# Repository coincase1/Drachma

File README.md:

30% Left-Handed Hall Effect Keypad

Based on / Inspired by [Peppapigh's HE60](https://github.com/peppapighs/HE60).

This keyboard is a PCB swap of the [Kisnt 34 Key Numpad](https://www.amazon.com/gp/product/B0C1H8V52D?smid=A1QSA46GV4FLI2&psc=1). With modifications to the top of the case using a hobby saw, this PCB fits inside of that case. The Drachma PCB connects to the Kisnt USB daughterboard using the provided Flat Conductor Cable. It also features a connection for a Pico-EZmate connector featured on Unified Daughterboards.

For anyone looking at this design at a later date, please be mindful of the Analog-to-Digital pins on the STM32F446 microcontroller. These can be verified on Sheets 46-56 of the STM32F446T MC Manual.

For HE switches, my recommendation are either OH49E-S or SS39ET from Honeywell. The OH49E-S are clones of these switches and these are featured in a number of big box HE board builds.

All Kicad and Firmware represents the latest (V3) Drachma build.

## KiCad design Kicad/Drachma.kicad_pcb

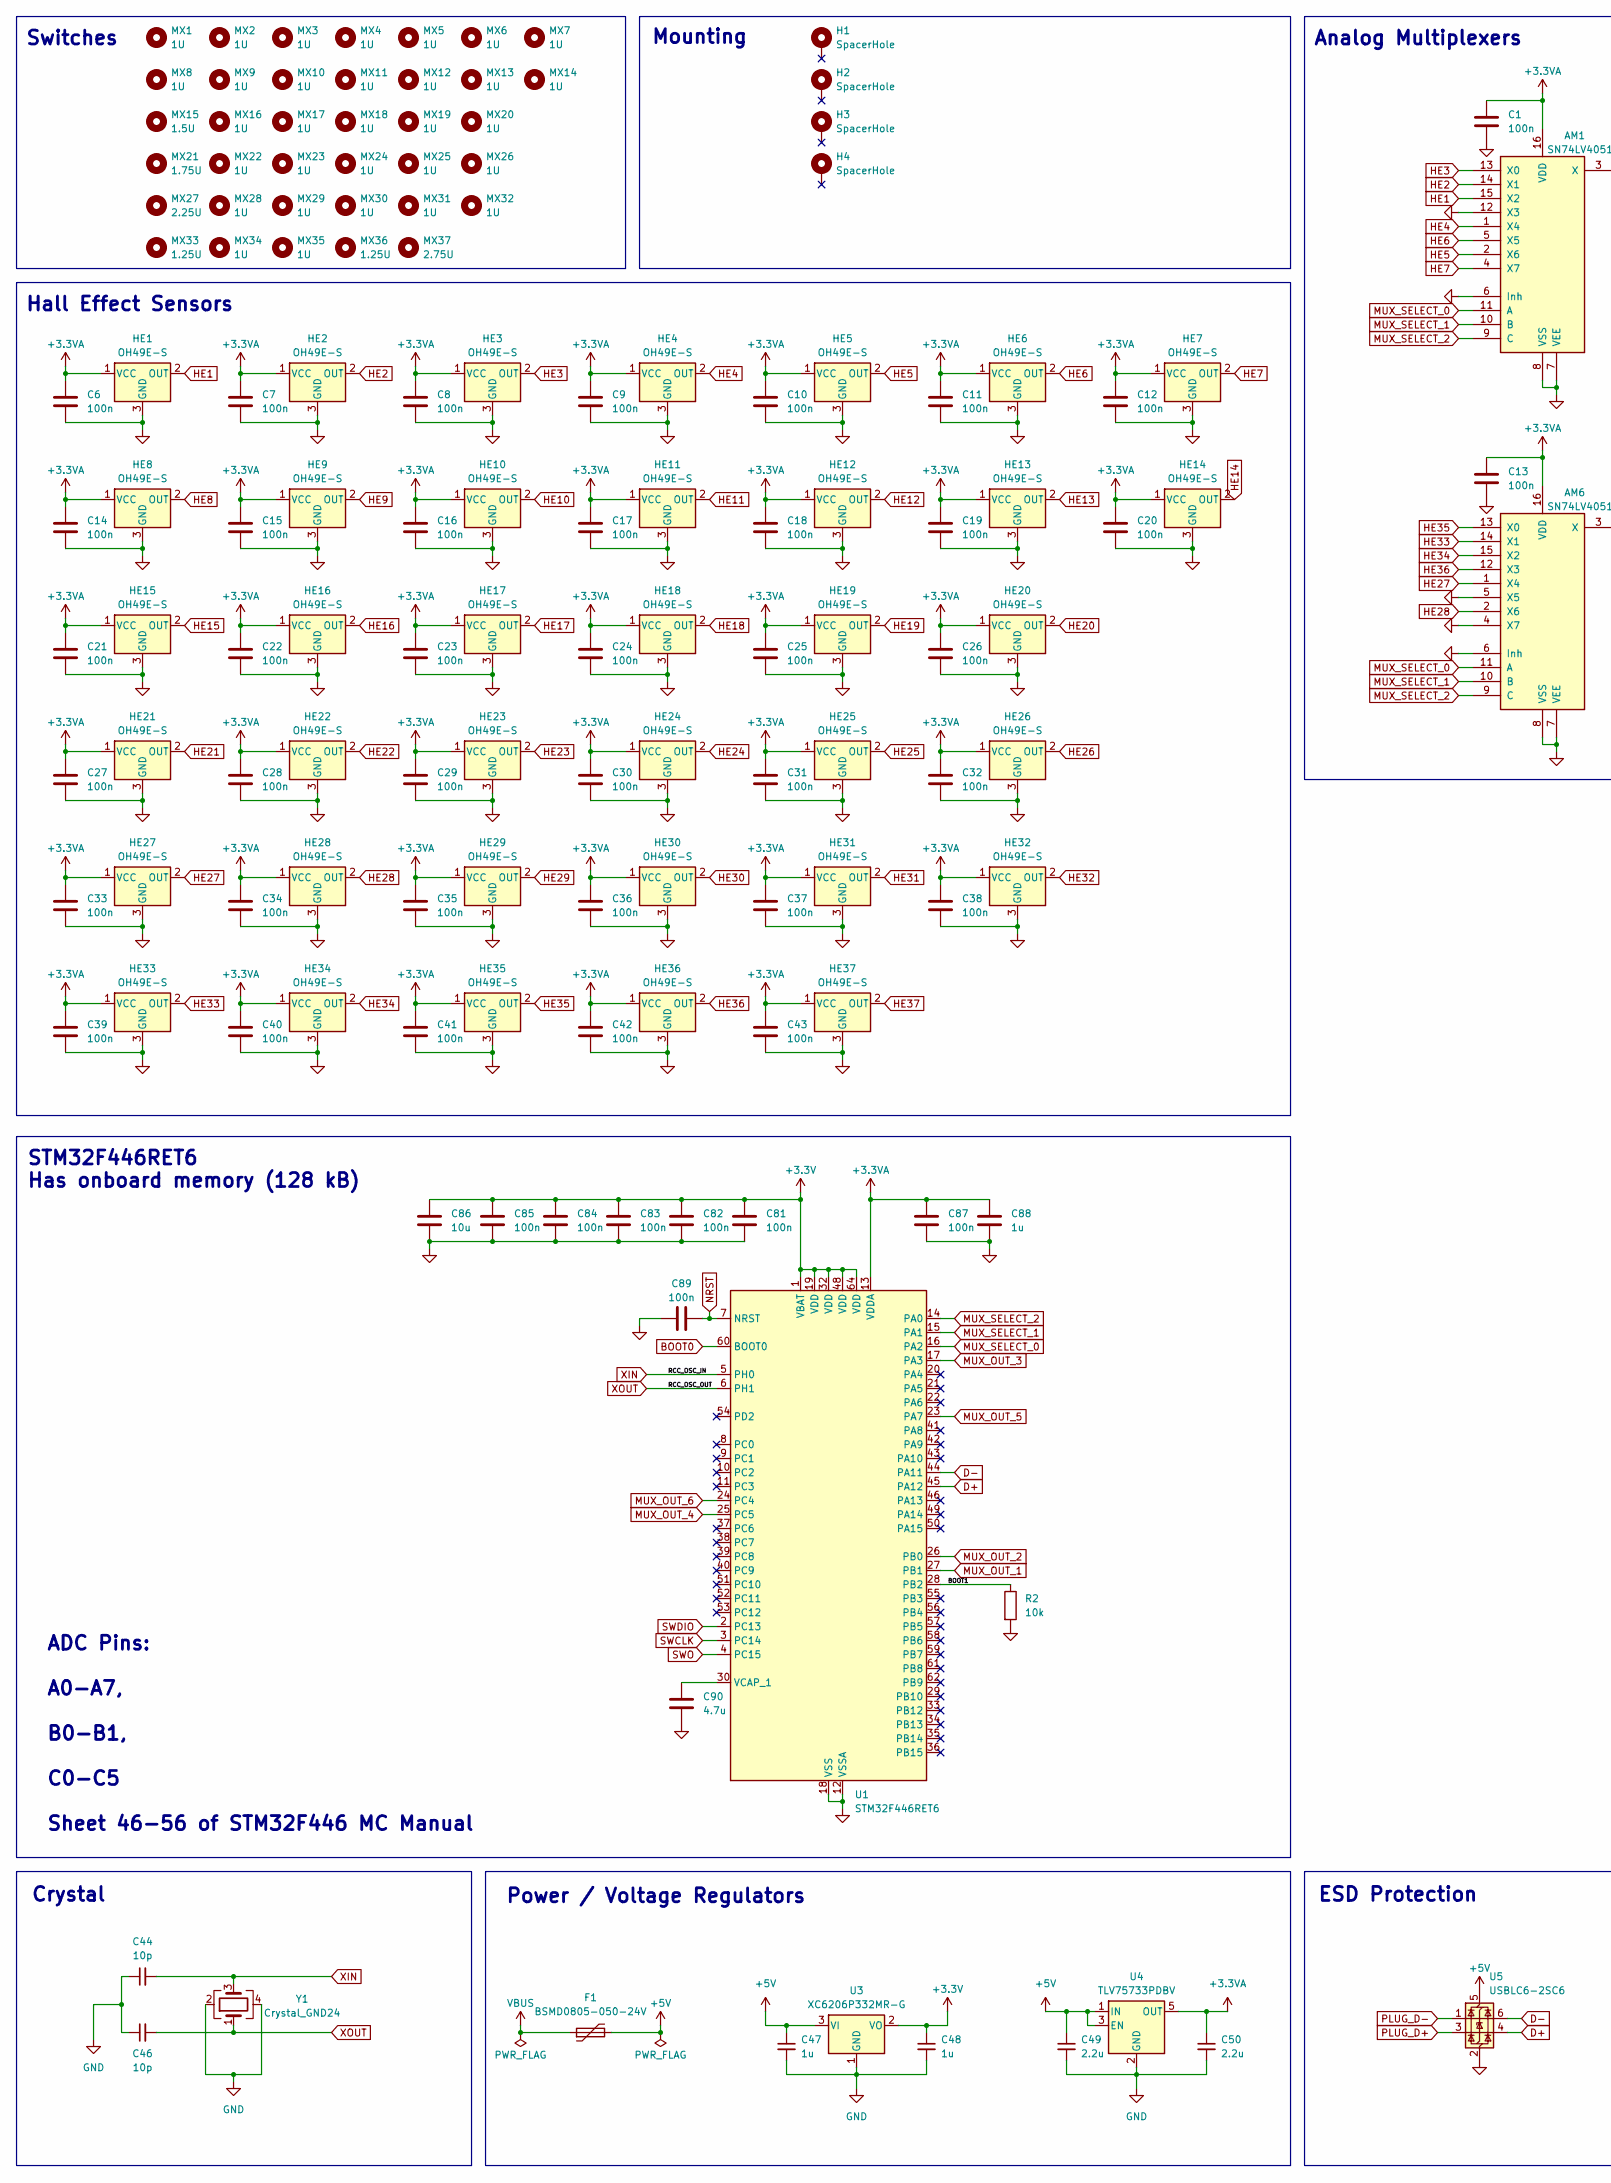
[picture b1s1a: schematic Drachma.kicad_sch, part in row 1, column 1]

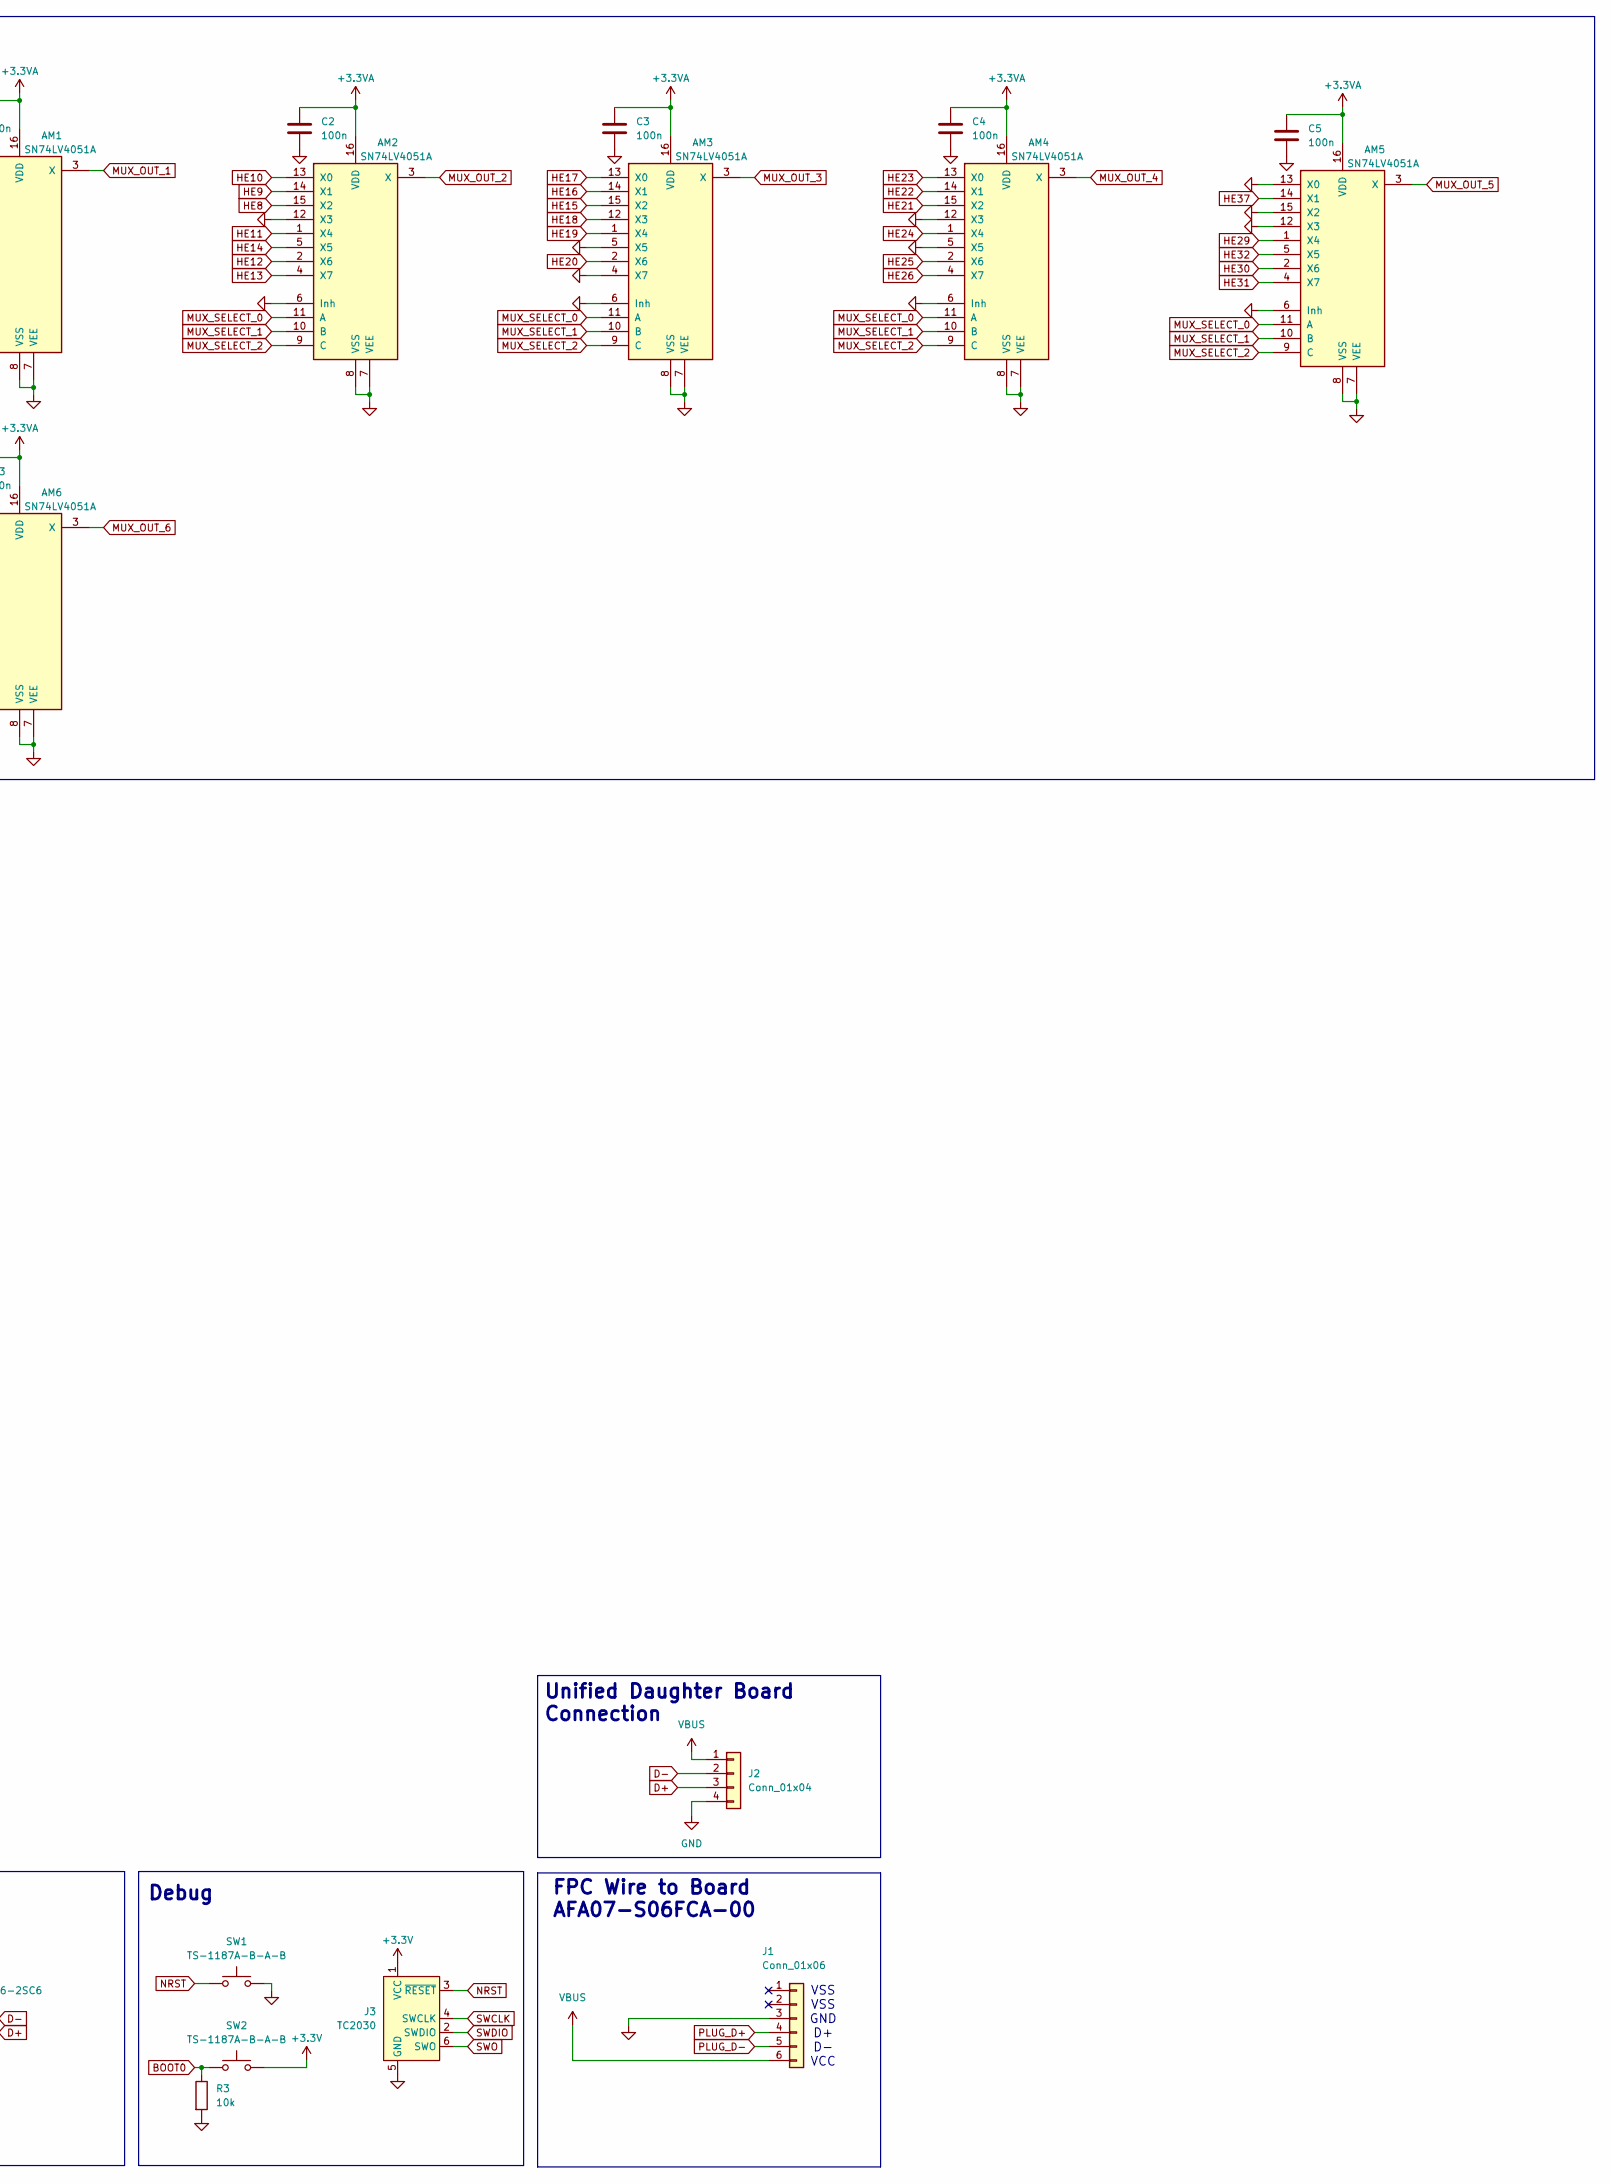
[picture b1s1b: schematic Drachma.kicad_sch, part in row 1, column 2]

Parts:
AM1, AM2, AM3, AM4, AM5, AM6: SN74LV4051A; TSSOP-16_4.4x5mm_P0.65mm
C1, C2, C3, C4, C5, C6, C7, C8, C9, C10, C11, C12, C13, C14, C15, C16, C17, C18, C19, C20, C21, C22, C23, C24, C25, C26, C27, C28, C29, C30, C31, C32, C33, C34, C35, C36, C37, C38, C39, C40, C41, C42, C43, C81, C82, C83, C84, C85, C87, C89: 100n; C_0402_1005Metric
C44, C46: 10p; C_0402_1005Metric
C47, C48, C88: 1u; C_0603_1608Metric
C49, C50: 2.2u; C_0603_1608Metric
C86: 10u; C_0603_1608Metric
C90: 4.7u; C_0603_1608Metric
F1: BSMD0805-050-24V; Fuse_0805_2012Metric
H1, H2, H3, H4: SpacerHole; MountingHole_2.2mm_M2_Pad
HE1, HE2, HE3, HE4, HE5, HE6, HE7, HE8, HE9, HE10, HE11, HE12, HE13, HE14, HE15, HE16, HE17, HE18, HE19, HE20, HE21, HE22, HE23, HE24, HE25, HE26, HE27, HE28, HE29, HE30, HE31, HE32, HE33, HE34, HE35, HE36, HE37: OH49E-S; SOT-23-3
J1: Conn_01x06; JUSHUO_AFA07-S06FCA-00_1x6-1MP_P1.0mm_Horizontal
J2: Conn_01x04; Molex_Pico-EZmate_78171-0004_1x04-1MP_P1.20mm_Vertical
J3: TC2030; Tag-Connect_TC2030-IDC-FP_2x03_P1.27mm_Vertical
MX1, MX2, MX3, MX4, MX5, MX6, MX7, MX8, MX9, MX10, MX11, MX12, MX13, MX14, MX16, MX17, MX18, MX19, MX20, MX22, MX23, MX24, MX25, MX26, MX28, MX29, MX30, MX31, MX32, MX34, MX35: 1U; MX-1U
MX15: 1.5U; MX-1.5U
MX21: 1.75U; MX-1.75U
MX27: 2.25U; MX-2.25U
MX33, MX36: 1.25U; MX-1.25U
MX37: 2.75U; MX-2.75U-ReversedStabilizers
R2, R3: 10k; R_0402_1005Metric
SW1, SW2: TS-1187A-B-A-B; SW_Push_1P1T_XKB_TS-1187A
U1: STM32F446RET6; LQFP-64_10x10mm_P0.5mm
U3: XC6206P332MR-G; SOT-23-3
U4: TLV75733PDBV; SOT-23-5
U5: USBLC6-2SC6; SOT-23-6
Y1: Crystal_GND24; Crystal_SMD_3225-4Pin_3.2x2.5mm

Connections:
+3.3V: C48.1, C81.1, C82.1, C83.1, C84.1, C85.1, C86.1, J3.1 (VCC), SW2.2, U1.1 (VBAT), U1.19 (VDD), U1.32 (VDD), U1.48 (VDD), U1.64 (VDD), U3.2 (VO)
+3.3VA: AM1.16 (VDD), AM2.16 (VDD), AM3.16 (VDD), AM4.16 (VDD), AM5.16 (VDD), AM6.16 (VDD), C1.1, C2.1, C3.1, C4.1, C5.1, C6.1, C7.1, C8.1, C9.1, C10.1, C11.1, C12.1, C13.1, C14.1, C15.1, C16.1, C17.1, C18.1, C19.1, C20.1, C21.1, C22.1, C23.1, C24.1, C25.1, C26.1, C27.1, C28.1, C29.1, C30.1, C31.1, C32.1, C33.1, C34.1, C35.1, C36.1, C37.1, C38.1, C39.1, C40.1, C41.1, C42.1, C43.1, C50.1, C87.1, C88.1, HE1.1 (VCC), HE2.1 (VCC), HE3.1 (VCC), HE4.1 (VCC), HE5.1 (VCC), HE6.1 (VCC), HE7.1 (VCC), HE8.1 (VCC), HE9.1 (VCC), HE10.1 (VCC), HE11.1 (VCC), HE12.1 (VCC), HE13.1 (VCC), HE14.1 (VCC), HE15.1 (VCC), HE16.1 (VCC), HE17.1 (VCC), HE18.1 (VCC), HE19.1 (VCC), HE20.1 (VCC), HE21.1 (VCC), HE22.1 (VCC), HE23.1 (VCC), HE24.1 (VCC), HE25.1 (VCC), HE26.1 (VCC), HE27.1 (VCC), HE28.1 (VCC), HE29.1 (VCC), HE30.1 (VCC), HE31.1 (VCC), HE32.1 (VCC), HE33.1 (VCC), HE34.1 (VCC), HE35.1 (VCC), HE36.1 (VCC), HE37.1 (VCC), U1.13 (VDDA), U4.5 (OUT)
+5V: C47.1, C49.1, F1.2, U3.3 (VI), U4.1 (IN), U4.3 (EN), U5.5 (VBUS)
/BOOT1: R2.1, U1.28 (PB2)
BOOT0: R3.1, SW2.1, U1.60 (BOOT0)
D+: J2.3, U1.45 (PA12), U5.4 (I/O2)
D-: J2.2, U1.44 (PA11), U5.6 (I/O1)
GND: AM1.6 (Inh), AM1.7 (VEE), AM1.8 (VSS), AM1.12 (X3), AM2.6 (Inh), AM2.7 (VEE), AM2.8 (VSS), AM2.12 (X3), AM3.4 (X7), AM3.5 (X5), AM3.6 (Inh), AM3.7 (VEE), AM3.8 (VSS), AM4.5 (X5), AM4.6 (Inh), AM4.7 (VEE), AM4.8 (VSS), AM4.12 (X3), AM5.6 (Inh), AM5.7 (VEE), AM5.8 (VSS), AM5.12 (X3), AM5.13 (X0), AM5.15 (X2), AM6.4 (X7), AM6.5 (X5), AM6.6 (Inh), AM6.7 (VEE), AM6.8 (VSS), C1.2, C2.2, C3.2, C4.2, C5.2, C6.2, C7.2, C8.2, C9.2, C10.2, C11.2, C12.2, C13.2, C14.2, C15.2, C16.2, C17.2, C18.2, C19.2, C20.2, C21.2, C22.2, C23.2, C24.2, C25.2, C26.2, C27.2, C28.2, C29.2, C30.2, C31.2, C32.2, C33.2, C34.2, C35.2, C36.2, C37.2, C38.2, C39.2, C40.2, C41.2, C42.2, C43.2, C44.1, C46.1, C47.2, C48.2, C49.2, C50.2, C81.2, C82.2, C83.2, C84.2, C85.2, C86.2, C87.2, C88.2, C89.1, C90.2, HE1.3 (GND), HE2.3 (GND), HE3.3 (GND), HE4.3 (GND), HE5.3 (GND), HE6.3 (GND), HE7.3 (GND), HE8.3 (GND), HE9.3 (GND), HE10.3 (GND), HE11.3 (GND), HE12.3 (GND), HE13.3 (GND), HE14.3 (GND), HE15.3 (GND), HE16.3 (GND), HE17.3 (GND), HE18.3 (GND), HE19.3 (GND), HE20.3 (GND), HE21.3 (GND), HE22.3 (GND), HE23.3 (GND), HE24.3 (GND), HE25.3 (GND), HE26.3 (GND), HE27.3 (GND), HE28.3 (GND), HE29.3 (GND), HE30.3 (GND), HE31.3 (GND), HE32.3 (GND), HE33.3 (GND), HE34.3 (GND), HE35.3 (GND), HE36.3 (GND), HE37.3 (GND), J1.3, J2.4, J3.5 (GND), R2.2, R3.2, SW1.2, U1.12 (VSSA), U1.18 (VSS), U1.31 (VSS), U1.47 (VSS), U1.63 (VSS), U3.1 (GND), U4.2 (GND), U5.2 (GND), Y1.2, Y1.4
HE1: AM1.15 (X2), HE1.2 (OUT)
HE2: AM1.14 (X1), HE2.2 (OUT)
HE3: AM1.13 (X0), HE3.2 (OUT)
HE4: AM1.1 (X4), HE4.2 (OUT)
HE5: AM1.2 (X6), HE5.2 (OUT)
HE6: AM1.5 (X5), HE6.2 (OUT)
HE7: AM1.4 (X7), HE7.2 (OUT)
HE8: AM2.15 (X2), HE8.2 (OUT)
HE9: AM2.14 (X1), HE9.2 (OUT)
HE10: AM2.13 (X0), HE10.2 (OUT)
HE11: AM2.1 (X4), HE11.2 (OUT)
HE12: AM2.2 (X6), HE12.2 (OUT)
HE13: AM2.4 (X7), HE13.2 (OUT)
HE14: AM2.5 (X5), HE14.2 (OUT)
HE15: AM3.15 (X2), HE15.2 (OUT)
HE16: AM3.14 (X1), HE16.2 (OUT)
HE17: AM3.13 (X0), HE17.2 (OUT)
HE18: AM3.12 (X3), HE18.2 (OUT)
HE19: AM3.1 (X4), HE19.2 (OUT)
HE20: AM3.2 (X6), HE20.2 (OUT)
HE21: AM4.15 (X2), HE21.2 (OUT)
HE22: AM4.14 (X1), HE22.2 (OUT)
HE23: AM4.13 (X0), HE23.2 (OUT)
HE24: AM4.1 (X4), HE24.2 (OUT)
HE25: AM4.2 (X6), HE25.2 (OUT)
HE26: AM4.4 (X7), HE26.2 (OUT)
HE27: AM6.1 (X4), HE27.2 (OUT)
HE28: AM6.2 (X6), HE28.2 (OUT)
HE29: AM5.1 (X4), HE29.2 (OUT)
HE30: AM5.2 (X6), HE30.2 (OUT)
HE31: AM5.4 (X7), HE31.2 (OUT)
HE32: AM5.5 (X5), HE32.2 (OUT)
HE33: AM6.14 (X1), HE33.2 (OUT)
HE34: AM6.15 (X2), HE34.2 (OUT)
HE35: AM6.13 (X0), HE35.2 (OUT)
HE36: AM6.12 (X3), HE36.2 (OUT)
HE37: AM5.14 (X1), HE37.2 (OUT)
MUX_OUT_1: AM1.3 (X), U1.27 (PB1)
MUX_OUT_2: AM2.3 (X), U1.26 (PB0)
MUX_OUT_3: AM3.3 (X), U1.17 (PA3)
MUX_OUT_4: AM4.3 (X), U1.25 (PC5)
MUX_OUT_5: AM5.3 (X), U1.23 (PA7)
MUX_OUT_6: AM6.3 (X), U1.24 (PC4)
MUX_SELECT_0: AM1.11 (A), AM2.11 (A), AM3.11 (A), AM4.11 (A), AM5.11 (A), AM6.11 (A), U1.16 (PA2)
MUX_SELECT_1: AM1.10 (B), AM2.10 (B), AM3.10 (B), AM4.10 (B), AM5.10 (B), AM6.10 (B), U1.15 (PA1)
MUX_SELECT_2: AM1.9 (C), AM2.9 (C), AM3.9 (C), AM4.9 (C), AM5.9 (C), AM6.9 (C), U1.14 (PA0)
NRST: C89.2, J3.3 (~RESET), SW1.1, U1.7 (NRST)
unnamed: C90.1, U1.30 (VCAP_1)
PLUG_D+: J1.4, U5.3 (I/O2)
PLUG_D-: J1.5, U5.1 (I/O1)
SWCLK: J3.4 (SWCLK), U1.3 (PC14)
SWDIO: J3.2 (SWDIO), U1.2 (PC13)
SWO: J3.6 (SWO), U1.4 (PC15)
VBUS: F1.1, J1.6, J2.1
XIN: C44.2, U1.5 (PH0), Y1.3
XOUT: C46.2, U1.6 (PH1), Y1.1

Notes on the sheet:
VSS VSS GND D+ D- VCC
STM32F446RET6 Has onboard memory (128 kB)
Mounting
ESD Protection
Switches
FPC Wire to Board AFA07-S06FCA-00
ADC Pins: A0-A7, B0-B1, C0-C5 Sheet 46-56 of STM32F446 MC Manual
Analog Multiplexers
Hall Effect Sensors
Unified Daughter Board Connection
Power / Voltage Regulators
Crystal
Debug

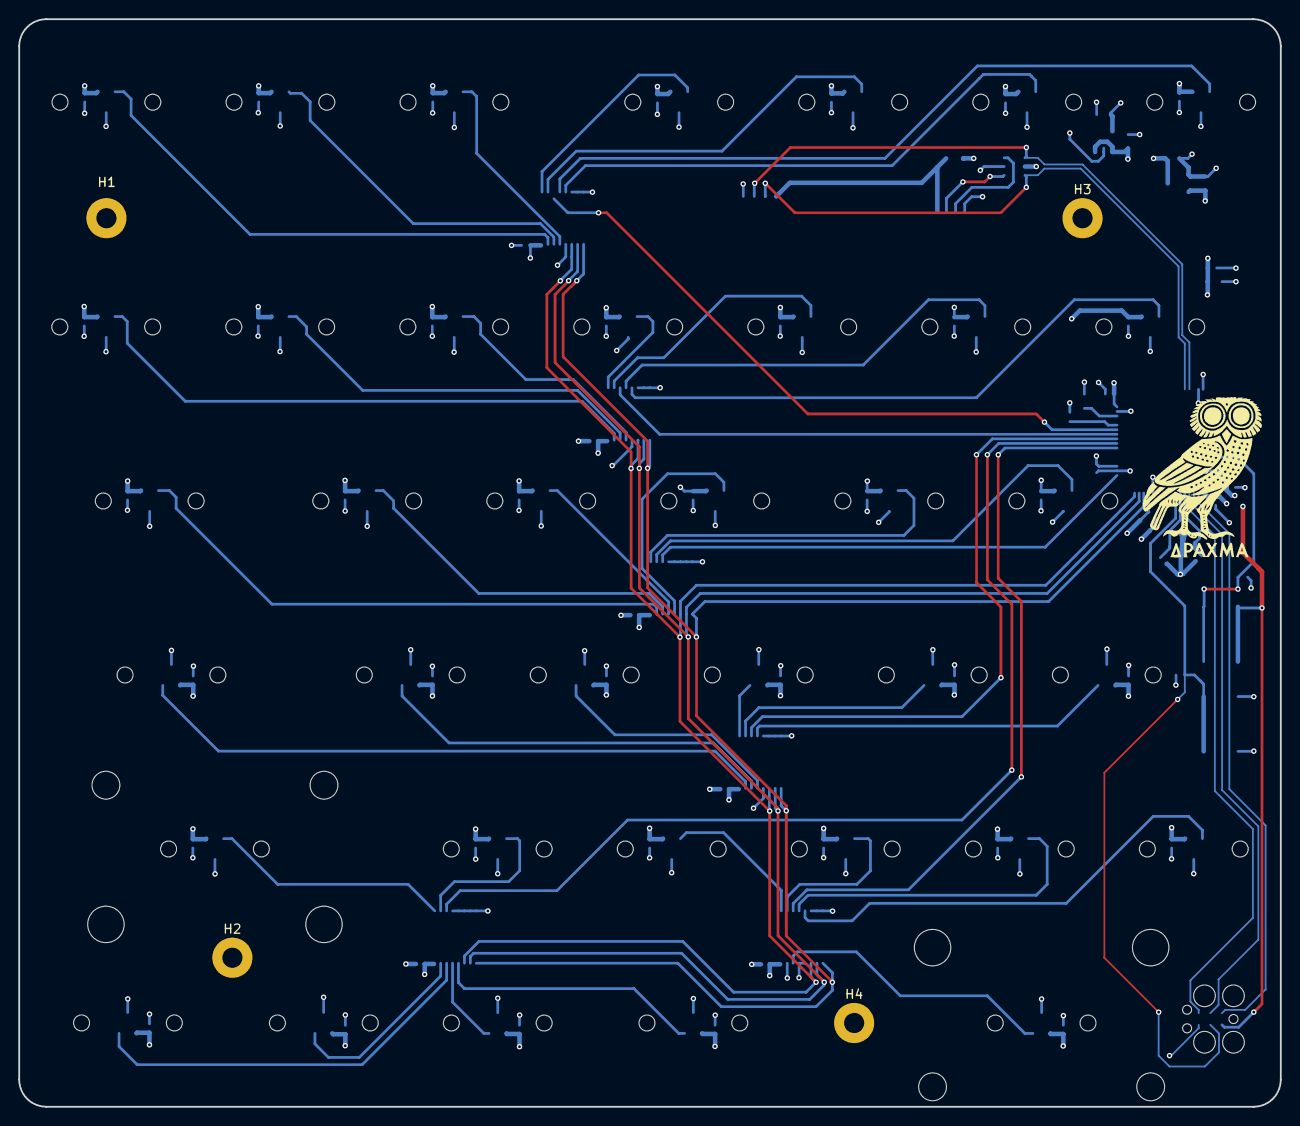
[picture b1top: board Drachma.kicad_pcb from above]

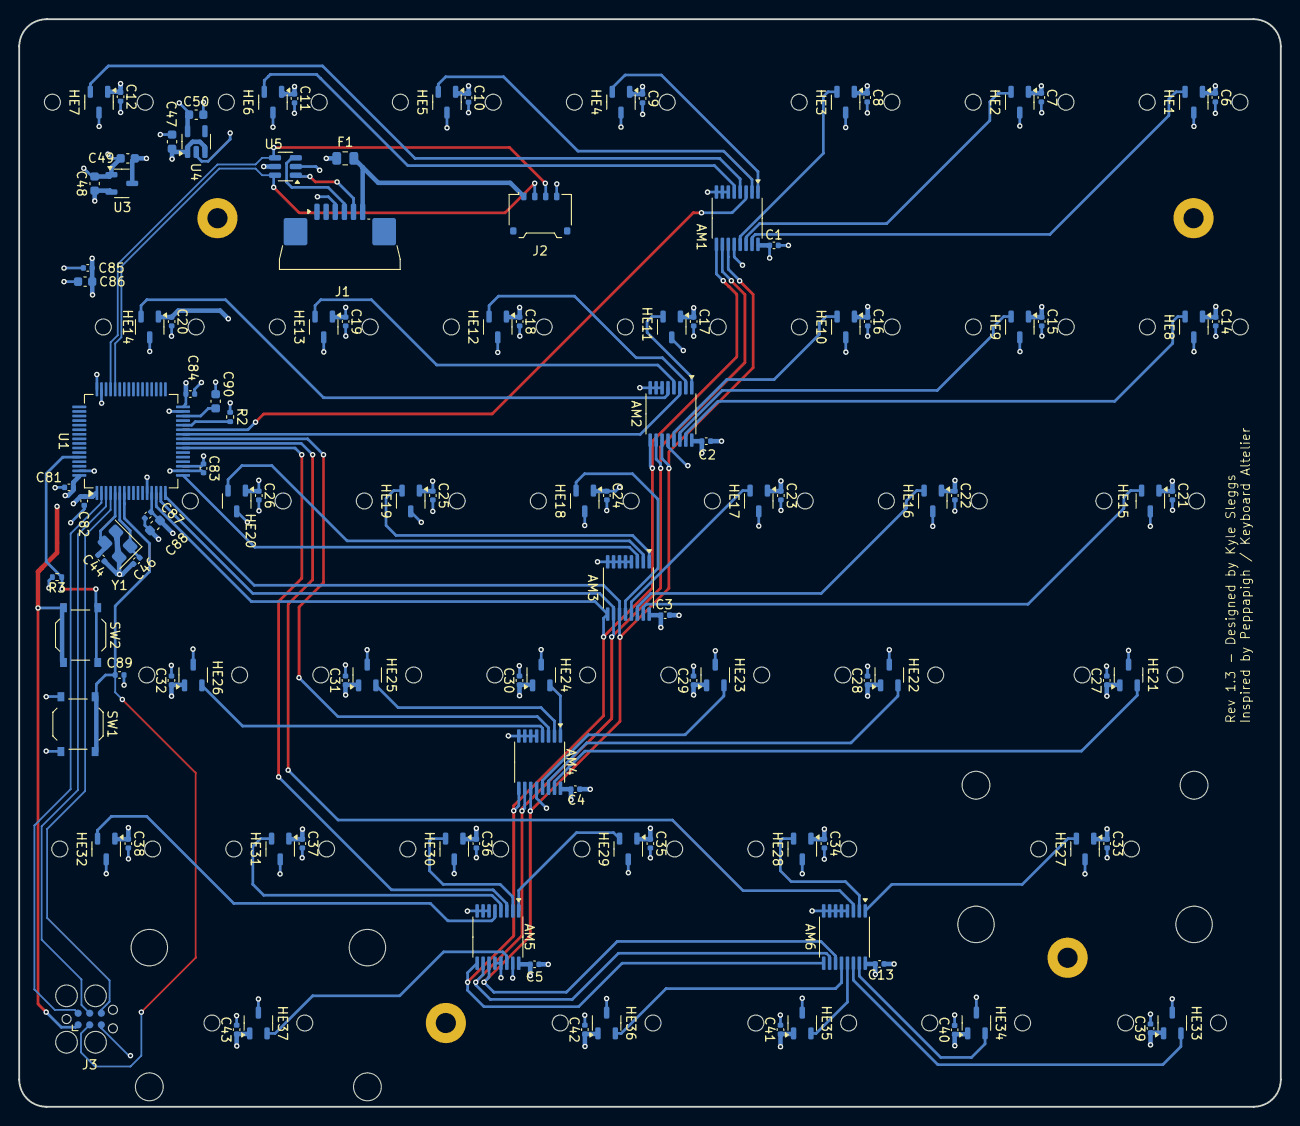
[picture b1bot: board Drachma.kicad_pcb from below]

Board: 4 copper layers, 138.1 x 119.1 mm, 156 parts (115 on the bottom side), 64 nets.

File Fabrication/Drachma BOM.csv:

Comment,Designator,Value,Footprint,JLCPCB Part #
Analog Multiplexer,AM1,SN74LV4051A,TSSOP-16_4.4x5mm_P0.65mm,C7793 
Analog Multiplexer,AM2,SN74LV4051A,TSSOP-16_4.4x5mm_P0.65mm,C7793 
Analog Multiplexer,AM3,SN74LV4051A,TSSOP-16_4.4x5mm_P0.65mm,C7793 
Analog Multiplexer,AM4,SN74LV4051A,TSSOP-16_4.4x5mm_P0.65mm,C7793 
Analog Multiplexer,AM5,SN74LV4051A,TSSOP-16_4.4x5mm_P0.65mm,C7793 
Analog Multiplexer,AM6,SN74LV4051A,TSSOP-16_4.4x5mm_P0.65mm,C7793 
100n,C1,100n,C_0402_1005Metric,C1525 
100n,C2,100n,C_0402_1005Metric,C1525 
100n,C3,100n,C_0402_1005Metric,C1525 
100n,C4,100n,C_0402_1005Metric,C1525 
100n,C5,100n,C_0402_1005Metric,C1525 
100n,C6,100n,C_0402_1005Metric,C1525 
100n,C7,100n,C_0402_1005Metric,C1525 
100n,C8,100n,C_0402_1005Metric,C1525 
100n,C9,100n,C_0402_1005Metric,C1525 
100n,C10,100n,C_0402_1005Metric,C1525 
100n,C11,100n,C_0402_1005Metric,C1525 
100n,C12,100n,C_0402_1005Metric,C1525 
100n,C13,100n,C_0402_1005Metric,C1525 
100n,C14,100n,C_0402_1005Metric,C1525 
100n,C15,100n,C_0402_1005Metric,C1525 
100n,C16,100n,C_0402_1005Metric,C1525 
100n,C17,100n,C_0402_1005Metric,C1525 
100n,C18,100n,C_0402_1005Metric,C1525 
100n,C19,100n,C_0402_1005Metric,C1525 
100n,C20,100n,C_0402_1005Metric,C1525 
100n,C21,100n,C_0402_1005Metric,C1525 
100n,C22,100n,C_0402_1005Metric,C1525 
100n,C23,100n,C_0402_1005Metric,C1525 
100n,C24,100n,C_0402_1005Metric,C1525 
100n,C25,100n,C_0402_1005Metric,C1525 
100n,C26,100n,C_0402_1005Metric,C1525 
100n,C27,100n,C_0402_1005Metric,C1525 
100n,C28,100n,C_0402_1005Metric,C1525 
100n,C29,100n,C_0402_1005Metric,C1525 
100n,C30,100n,C_0402_1005Metric,C1525 
100n,C31,100n,C_0402_1005Metric,C1525 
100n,C32,100n,C_0402_1005Metric,C1525 
100n,C33,100n,C_0402_1005Metric,C1525 
100n,C34,100n,C_0402_1005Metric,C1525 
100n,C35,100n,C_0402_1005Metric,C1525 
100n,C36,100n,C_0402_1005Metric,C1525 
100n,C37,100n,C_0402_1005Metric,C1525 
100n,C38,100n,C_0402_1005Metric,C1525 
100n,C39,100n,C_0402_1005Metric,C1525 
100n,C40,100n,C_0402_1005Metric,C1525 
100n,C41,100n,C_0402_1005Metric,C1525 
100n,C42,100n,C_0402_1005Metric,C1525 
100n,C43,100n,C_0402_1005Metric,C1525 
10p,C44,10p,C_0402_1005Metric,C32949 
10p,C46,10p,C_0402_1005Metric,C32949 
1u,C47,1u,C_0603_1608Metric,C15849 
1u,C48,1u,C_0603_1608Metric,C15849 
2.2u,C49,2.2u,C_0603_1608Metric,C23630 
2.2u,C50,2.2u,C_0603_1608Metric,C23630 
100n,C81,100n,C_0402_1005Metric,C1525 
100n,C82,100n,C_0402_1005Metric,C1525 
100n,C83,100n,C_0402_1005Metric,C1525 
100n,C84,100n,C_0402_1005Metric,C1525 
100n,C85,100n,C_0402_1005Metric,C1525 
10u,C86,10u,C_0603_1608Metric,C19702 
100n,C87,100n,C_0402_1005Metric,C1525 
1u,C88,1u,C_0603_1608Metric,C15849 
100n,C89,100n,C_0402_1005Metric,C1525 
4.7u,C90,4.7u,C_0603_1608Metric,C19666 
Fuse,F1,BSMD0805-050-24V,Fuse_0805_2012Metric,C910822 
Hall Effect Sensor,HE1,SS39ET ,SOT-23,C126669 
Hall Effect Sensor,HE2,SS39ET ,SOT-23,C126669 
Hall Effect Sensor,HE3,SS39ET ,SOT-23,C126669 
Hall Effect Sensor,HE4,SS39ET ,SOT-23,C126669 
Hall Effect Sensor,HE5,SS39ET ,SOT-23,C126669 
Hall Effect Sensor,HE6,SS39ET ,SOT-23,C126669 
Hall Effect Sensor,HE7,SS39ET ,SOT-23,C126669 
Hall Effect Sensor,HE8,SS39ET ,SOT-23,C126669 
Hall Effect Sensor,HE9,SS39ET ,SOT-23,C126669 
Hall Effect Sensor,HE10,SS39ET ,SOT-23,C126669 
Hall Effect Sensor,HE11,SS39ET ,SOT-23,C126669 
Hall Effect Sensor,HE12,SS39ET ,SOT-23,C126669 
Hall Effect Sensor,HE13,SS39ET ,SOT-23,C126669 
Hall Effect Sensor,HE14,SS39ET ,SOT-23,C126669 
Hall Effect Sensor,HE15,SS39ET ,SOT-23,C126669 
Hall Effect Sensor,HE16,SS39ET ,SOT-23,C126669 
Hall Effect Sensor,HE17,SS39ET ,SOT-23,C126669 
Hall Effect Sensor,HE18,SS39ET ,SOT-23,C126669 
Hall Effect Sensor,HE19,SS39ET ,SOT-23,C126669 
Hall Effect Sensor,HE20,SS39ET ,SOT-23,C126669 
Hall Effect Sensor,HE21,SS39ET ,SOT-23,C126669 
Hall Effect Sensor,HE22,SS39ET ,SOT-23,C126669 
Hall Effect Sensor,HE23,SS39ET ,SOT-23,C126669 
Hall Effect Sensor,HE24,SS39ET ,SOT-23,C126669 
Hall Effect Sensor,HE25,SS39ET ,SOT-23,C126669 
Hall Effect Sensor,HE26,SS39ET ,SOT-23,C126669 
Hall Effect Sensor,HE27,SS39ET ,SOT-23,C126669 
Hall Effect Sensor,HE28,SS39ET ,SOT-23,C126669 
Hall Effect Sensor,HE29,SS39ET ,SOT-23,C126669 
Hall Effect Sensor,HE30,SS39ET ,SOT-23,C126669 
Hall Effect Sensor,HE31,SS39ET ,SOT-23,C126669 
Hall Effect Sensor,HE32,SS39ET ,SOT-23,C126669 
Hall Effect Sensor,HE33,SS39ET ,SOT-23,C126669 
Hall Effect Sensor,HE34,SS39ET ,SOT-23,C126669 
Hall Effect Sensor,HE35,SS39ET ,SOT-23,C126669 
Hall Effect Sensor,HE36,SS39ET ,SOT-23,C126669 
Hall Effect Sensor,HE37,SS39ET ,SOT-23,C126669 
Conn_01x06,J1,,JUSHUO_AFA07-S06FCA-00_1x6-1MP_P1.0mm_Horizontal,C262712 
Conn_01x04,J2,,Molex_Pico-EZmate_78171-0004_1x04-1MP_P1.20mm_Vertical,C588524 
10k,R2,10k,R_0402_1005Metric,C25744 
10k,R3,10k,R_0402_1005Metric,C25744 
Switch,SW1,,SW_Push_1P1T_XKB_TS-1187A,C318884 
Switch,SW2,,SW_Push_1P1T_XKB_TS-1187A,C318884 
STM32F446RET6,U1,,LQFP-64_10x10mm_P0.5mm,C69336 
XC6206P332MR-G,U3,,SOT-23-3,C5446 
TLV75733PDBV,U4,,SOT-23-5,C485517 
USBLC6-2SC6,U5,,SOT-23-6,C7519 
X322516MLB4SI ,Y1,Crystal_GND24,Crystal_SMD_3225-4Pin_3.2x2.5mm,C13738

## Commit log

2026-01-08 Modify hardware settings and calibration values
    Updated hardware configuration and calibration values in keyboard.json.
2026-01-08 Rename Drachma_Back.jpg to Drachma V1_Back.jpg
2026-01-08 Rename Drachma_Front.jpg to Drachma V1_Front.jpg
2026-01-08 Create Kicad
2026-01-08 Fix link formatting in README.md
2026-01-08 Create txt
2026-01-08 Enhance README with keyboard design details
    Added detailed information about the keyboard's design, modifications, and component recommendations.
2026-01-08 Update README with Kicad and Firmware version info
    Added a note about Kicad and Firmware version.
2026-01-08 Rename Drachma V3_Front.jpg to Drachma V2_Front.jpg
2026-01-08 Update README with firmware purpose
    Added a brief description of the firmware's purpose.
2026-01-08 Add image link to Drachma Keyboard in README
    Added an image link for the Drachma Keyboard.
2026-01-08 Fix image link formatting in README.md
